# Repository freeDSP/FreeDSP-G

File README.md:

# FreeDSP-G (ADAU1467 DSP BOARD)

ADAU1467 DSP Board for Electic Guitar Players. The latest version design is 0.2  

## Features  

### Tube Electric Guitar Amplifier Simulator
* A simple single DSP board concept
* 6.5mm Phone Jack I/O connector
* KARAOKE (Play-along) feature
* Effect loop function with plug insert detection feature
* Stereo Output
* Headphones output
* Switchable Dual 7 Potentiometer Controls
* Dual Color LED indicator x1
* Single Color LED x1
* 3 Momentary-ON Footswitches with LED indicator
* Optical S/PDIF Input and Output
* 3.5mm Stereo Analog signal Input with plug insert detection and rotary volume control feature.
* USB-C Audio Input (44.1kHZ/48kHz)
* Embedded BM83 Bluetooth Audio Interface (Option)
* BGM mix level control (POT-7)
* DSP reset button
* Selfboot disable jumper
* Brite(Hi-Boost) Jumper
* Triodizer Head Amplifier with bypass option
* USBi 10P IDC pin-Header with Shoruld

Wiki Page: https://github.com/freeDSP/FreeDSP-G/wiki

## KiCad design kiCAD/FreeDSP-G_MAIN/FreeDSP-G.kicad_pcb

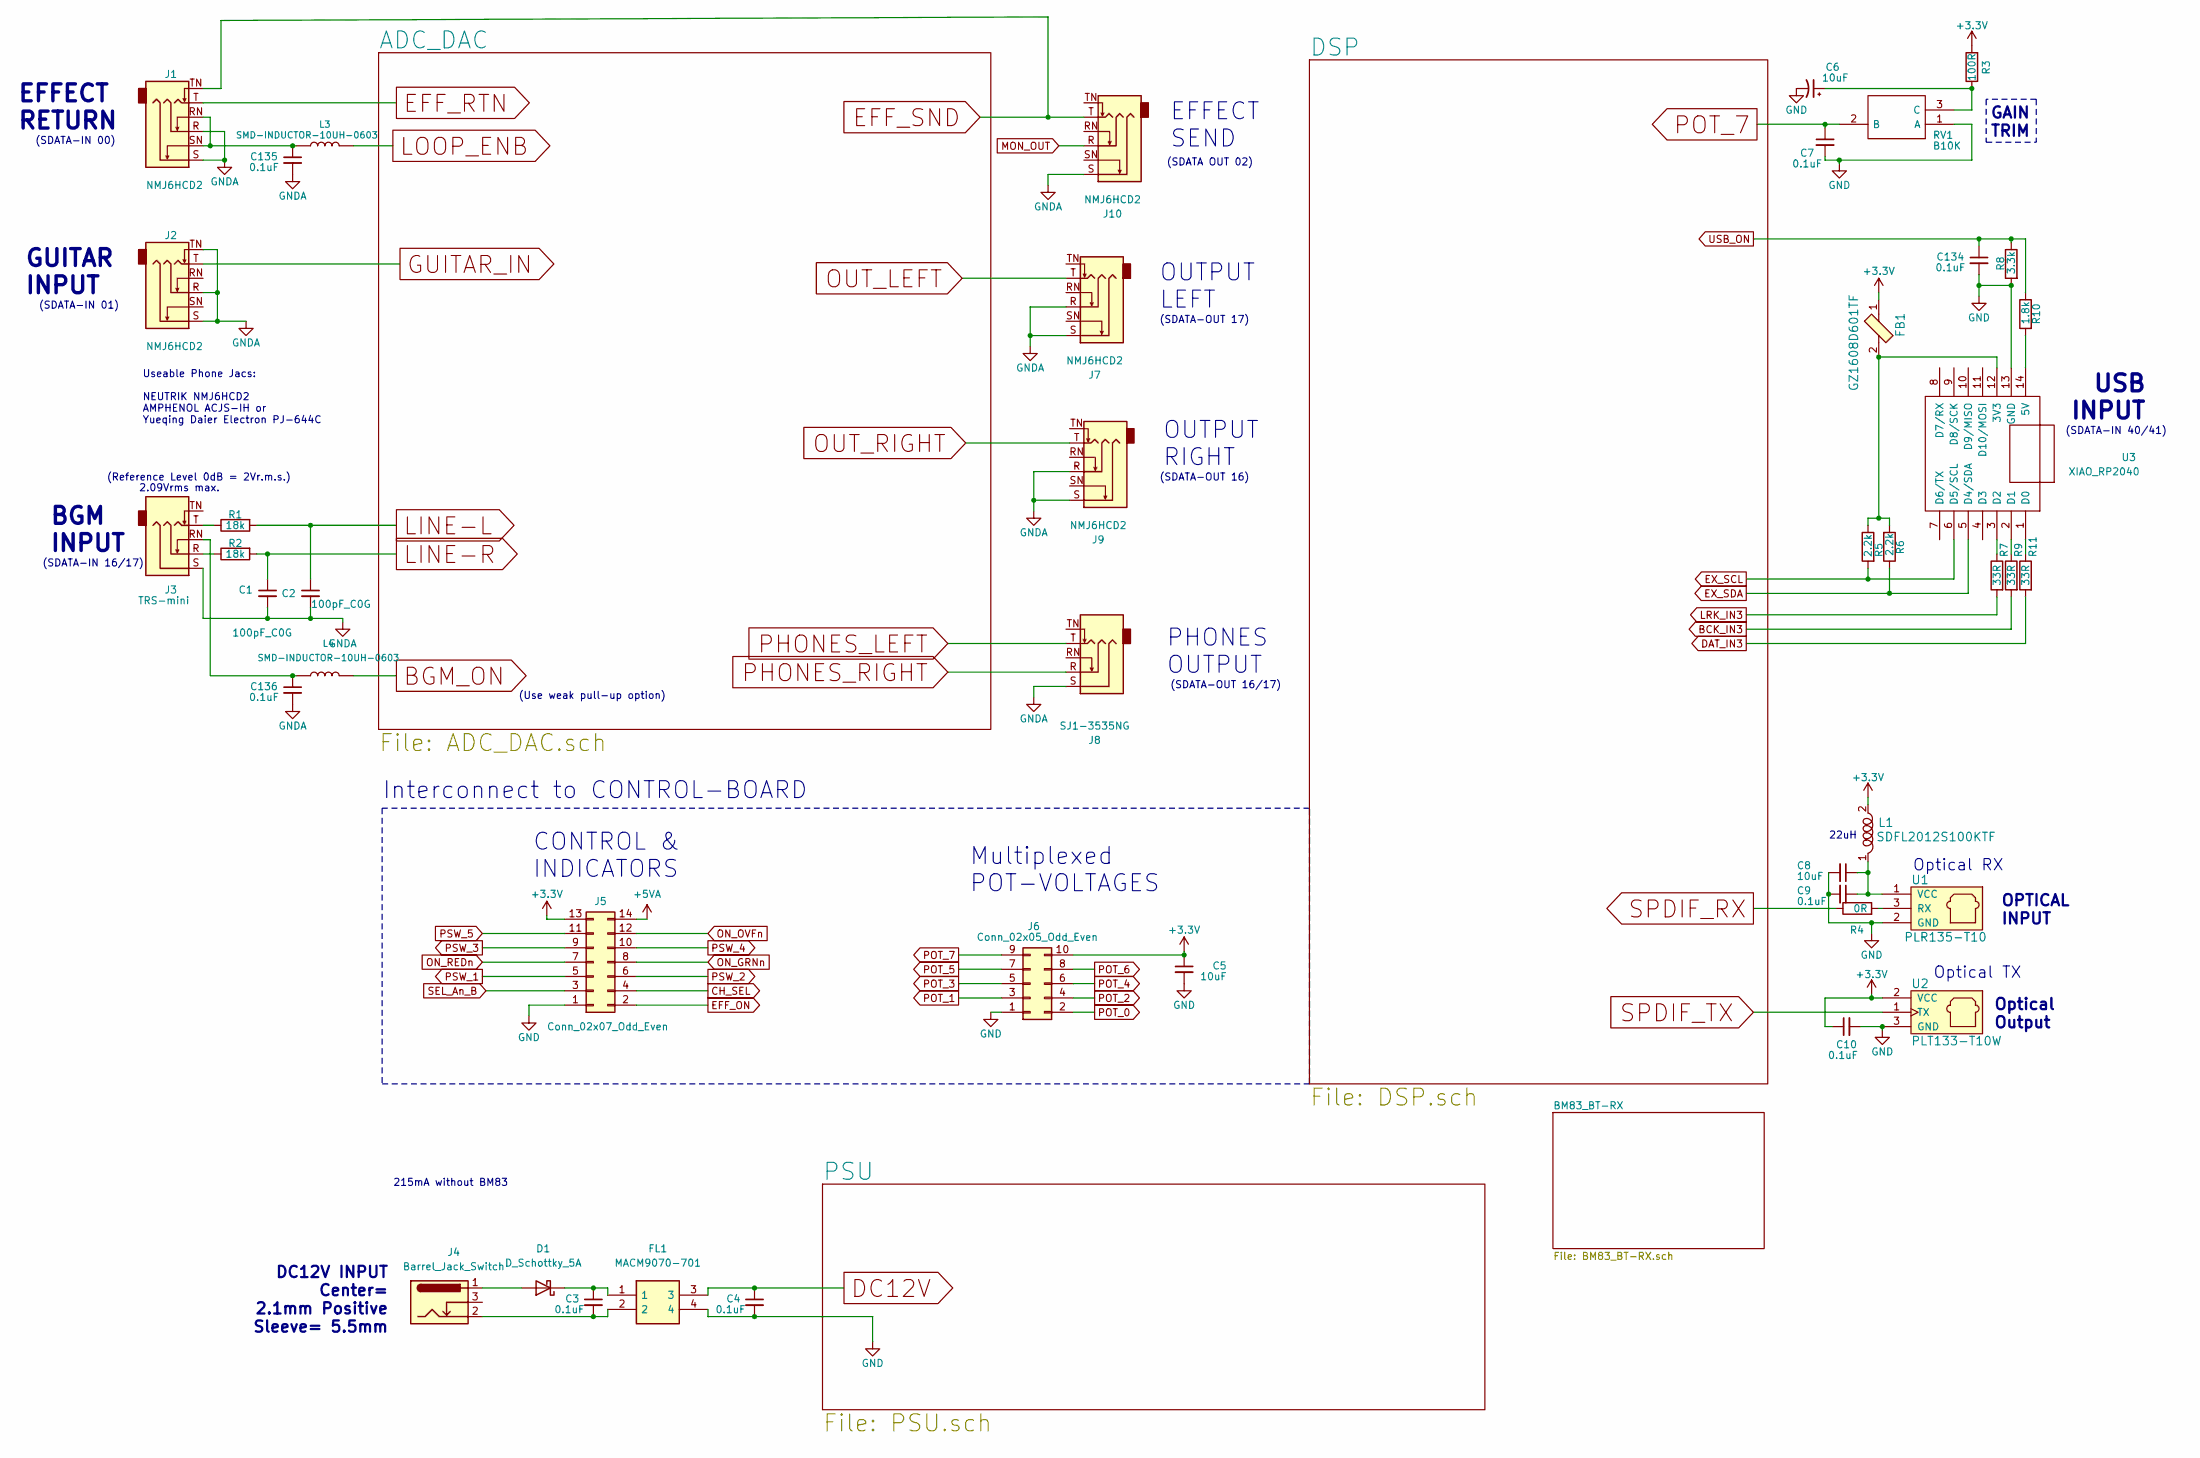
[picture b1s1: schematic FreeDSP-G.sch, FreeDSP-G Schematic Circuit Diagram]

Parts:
C1, C2: 100pF_C0G; C_0603_1608Metric_Pad1.08x0.95mm_HandSolder
C3, C4, C7, C9, C10, C134, C135, C136: 0.1uF; C_0603_1608Metric_Pad1.08x0.95mm_HandSolder
C5, C6, C8: 10uF; C_0805_2012Metric
D1: D_Schottky_5A; D_SMA
FB1: GZ1608D601TF; L_0603_1608Metric_Pad1.05x0.95mm_HandSolder; MPN BLM18AG601SN1D; Digi-Key_PN 490-1014-1-ND
FL1: MACM9070-701; ACM9070; Manufacturer_Part_Number ACM9070-701-2PL-TL01
J1, J2, J7, J9, J10: NMJ6HCD2; PJ-644C_NMJ6HCD2_ACJS-IH
J3: TRS-mini; Jack_3.5mm_CUI_SJ1-3535NG_Horizontal
J4: Barrel_Jack_Switch; BarrelJack_CUI_PJ-102AH_Horizontal
J5: Conn_02x07_Odd_Even; IDC-Header_2x07_P2.54mm_Horizontal
J6: Conn_02x05_Odd_Even; IDC-Header_2x05_P2.54mm_Horizontal
J8: SJ1-3535NG; Jack_3.5mm_CUI_SJ1-3535NG_Horizontal
L1: SDFL2012S100KTF; L_0805_2012Metric_Pad1.15x1.40mm_HandSolder; MPN 82473C; Digi-Key_PN 811-2477-1-ND
L3, L4: SMD-INDUCTOR-10UH-0603; L_0603_1608Metric; MPN SDFL1608S100KTF
R1, R2: 18k; R_0603_1608Metric_Pad0.98x0.95mm_HandSolder
R3: 100R; R_0603_1608Metric_Pad0.98x0.95mm_HandSolder
R4: 0R; R_0603_1608Metric_Pad0.98x0.95mm_HandSolder
R5, R6: 2.2k; R_0603_1608Metric_Pad0.98x0.95mm_HandSolder
R7, R9, R11: 33R; R_0603_1608Metric_Pad0.98x0.95mm_HandSolder
R8: 3.3k; R_0603_1608Metric_Pad0.98x0.95mm_HandSolder
R10: 1.8k; R_0603_1608Metric_Pad0.98x0.95mm_HandSolder
RV1: B10K; Potentiometer_Vishay_T73XX_Horizontal
U1: PLR135-T10
U2: PLT133-T10W
U3: XIAO_RP2040

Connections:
+3V3: C5.1, C10.1, FB1.1, J5.13, J6.10, L1.2, R3.2, U2.2 (VCC); also elsewhere on the board
+5VA: J5.14; also elsewhere on the board
BCK_IN3: R9.2; also elsewhere on the board
BGM_ON: L4.2; also elsewhere on the board
CH_SEL: J5.4; also elsewhere on the board
DAT_IN3: R11.2; also elsewhere on the board
DC12V: C4.1, FL1.3; also elsewhere on the board
EFF_ON: J5.2; also elsewhere on the board
EFF_RTN: J1.T; also elsewhere on the board
EFF_SND: J1.TN, J10.T; also elsewhere on the board
EX_SCL: R5.2, U3.6 (D5/SCL); also elsewhere on the board
EX_SDA: R6.1, U3.5 (D4/SDA); also elsewhere on the board
GND: C4.2, C5.2, C6.2, C7.2, C8.2, C9.2, C10.2, C134.2, FL1.4, J5.1, J6.1, R8.2, RV1.1 (A), U1.2 (GND), U2.3 (GND), U3.13 (GND); also elsewhere on the board
GNDA: C1.2, C2.2, C135.2, C136.2, J1.R, J1.S, J2.R, J2.S, J2.TN, J3.S, J7.R, J7.S, J8.S, J9.R, J9.S, J10.S; also elsewhere on the board
GUITAR_IN: J2.T; also elsewhere on the board
LINE-L: C2.1, R1.2; also elsewhere on the board
LINE-R: C1.1, R2.2; also elsewhere on the board
LOOP_ENB: L3.2; also elsewhere on the board
LRK_IN3: R7.2; also elsewhere on the board
MON_OUT: J10.R; also elsewhere on the board
unnamed: C3.1, D1.1 (K), FL1.1
unnamed: C3.2, FL1.2, J4.2
unnamed: C6.1, R3.1, RV1.3 (C)
unnamed: C8.1, C9.1, L1.1, U1.1 (VCC)
unnamed: C135.1, J1.RN, J1.SN, L3.1
unnamed: C136.1, J3.RN, L4.1
unnamed: D1.2 (A), J4.1
unnamed: FB1.2, R5.1, R6.2, U3.12 (3V3)
unnamed: J3.R, R2.1
unnamed: J3.T, R1.1
unnamed: R4.2, U1.3 (RX)
unnamed: R7.1, U3.3 (D2)
unnamed: R9.1, U3.2 (D1)
unnamed: R10.2, U3.14 (5V)
unnamed: R11.1, U3.1 (D0)
ON_GRNn: J5.8; also elsewhere on the board
ON_OVFn: J5.12; also elsewhere on the board
ON_REDn: J5.7; also elsewhere on the board
OUT_LEFT: J7.T; also elsewhere on the board
OUT_RIGHT: J9.T; also elsewhere on the board
PHONES_LEFT: J8.T; also elsewhere on the board
PHONES_RIGHT: J8.R; also elsewhere on the board
POT_0: J6.2; also elsewhere on the board
POT_1: J6.3; also elsewhere on the board
POT_2: J6.4; also elsewhere on the board
POT_3: J6.5; also elsewhere on the board
POT_4: J6.6; also elsewhere on the board
POT_5: J6.7; also elsewhere on the board
POT_6: J6.8; also elsewhere on the board
POT_7: C7.1, J6.9, RV1.2 (B); also elsewhere on the board
PSW_1: J5.5; also elsewhere on the board
PSW_2: J5.6; also elsewhere on the board
PSW_3: J5.9; also elsewhere on the board
PSW_4: J5.10; also elsewhere on the board
PSW_5: J5.11; also elsewhere on the board
SEL_An_B: J5.3; also elsewhere on the board
SPDIF_RX: R4.1; also elsewhere on the board
SPDIF_TX: U2.1 (TX); also elsewhere on the board
USB_ON: C134.1, R8.1, R10.1; also elsewhere on the board

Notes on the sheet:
DC12V INPUT Center= 2.1mm Positive Sleeve= 5.5mm
GUITAR INPUT
EFFECT RETURN
EFFECT SEND
PHONES OUTPUT
BGM INPUT
OUTPUT LEFT
OUTPUT RIGHT
(Reference Level 0dB = 2Vr.m.s.)
2.09Vrms max.
USB INPUT
CONTROL & INDICATORS
Multiplexed POT-VOLTAGES
Interconnect to CONTROL-BOARD
Optical Output
OPTICAL INPUT
22uH
Optical RX
Optical TX
GAIN TRIM
(Use weak pull-up option)
Useable Phone Jacs: NEUTRIK NMJ6HCD2 AMPHENOL ACJS-IH or Yueqing Daier Electron PJ-644C
215mA without BM83
(SDATA-IN 01)
(SDATA-IN 00)
(SDATA-IN 16/17)
(SDATA-IN 40/41)
(SDATA OUT 02)
(SDATA-OUT 17)
(SDATA-OUT 16)
(SDATA-OUT 16/17)

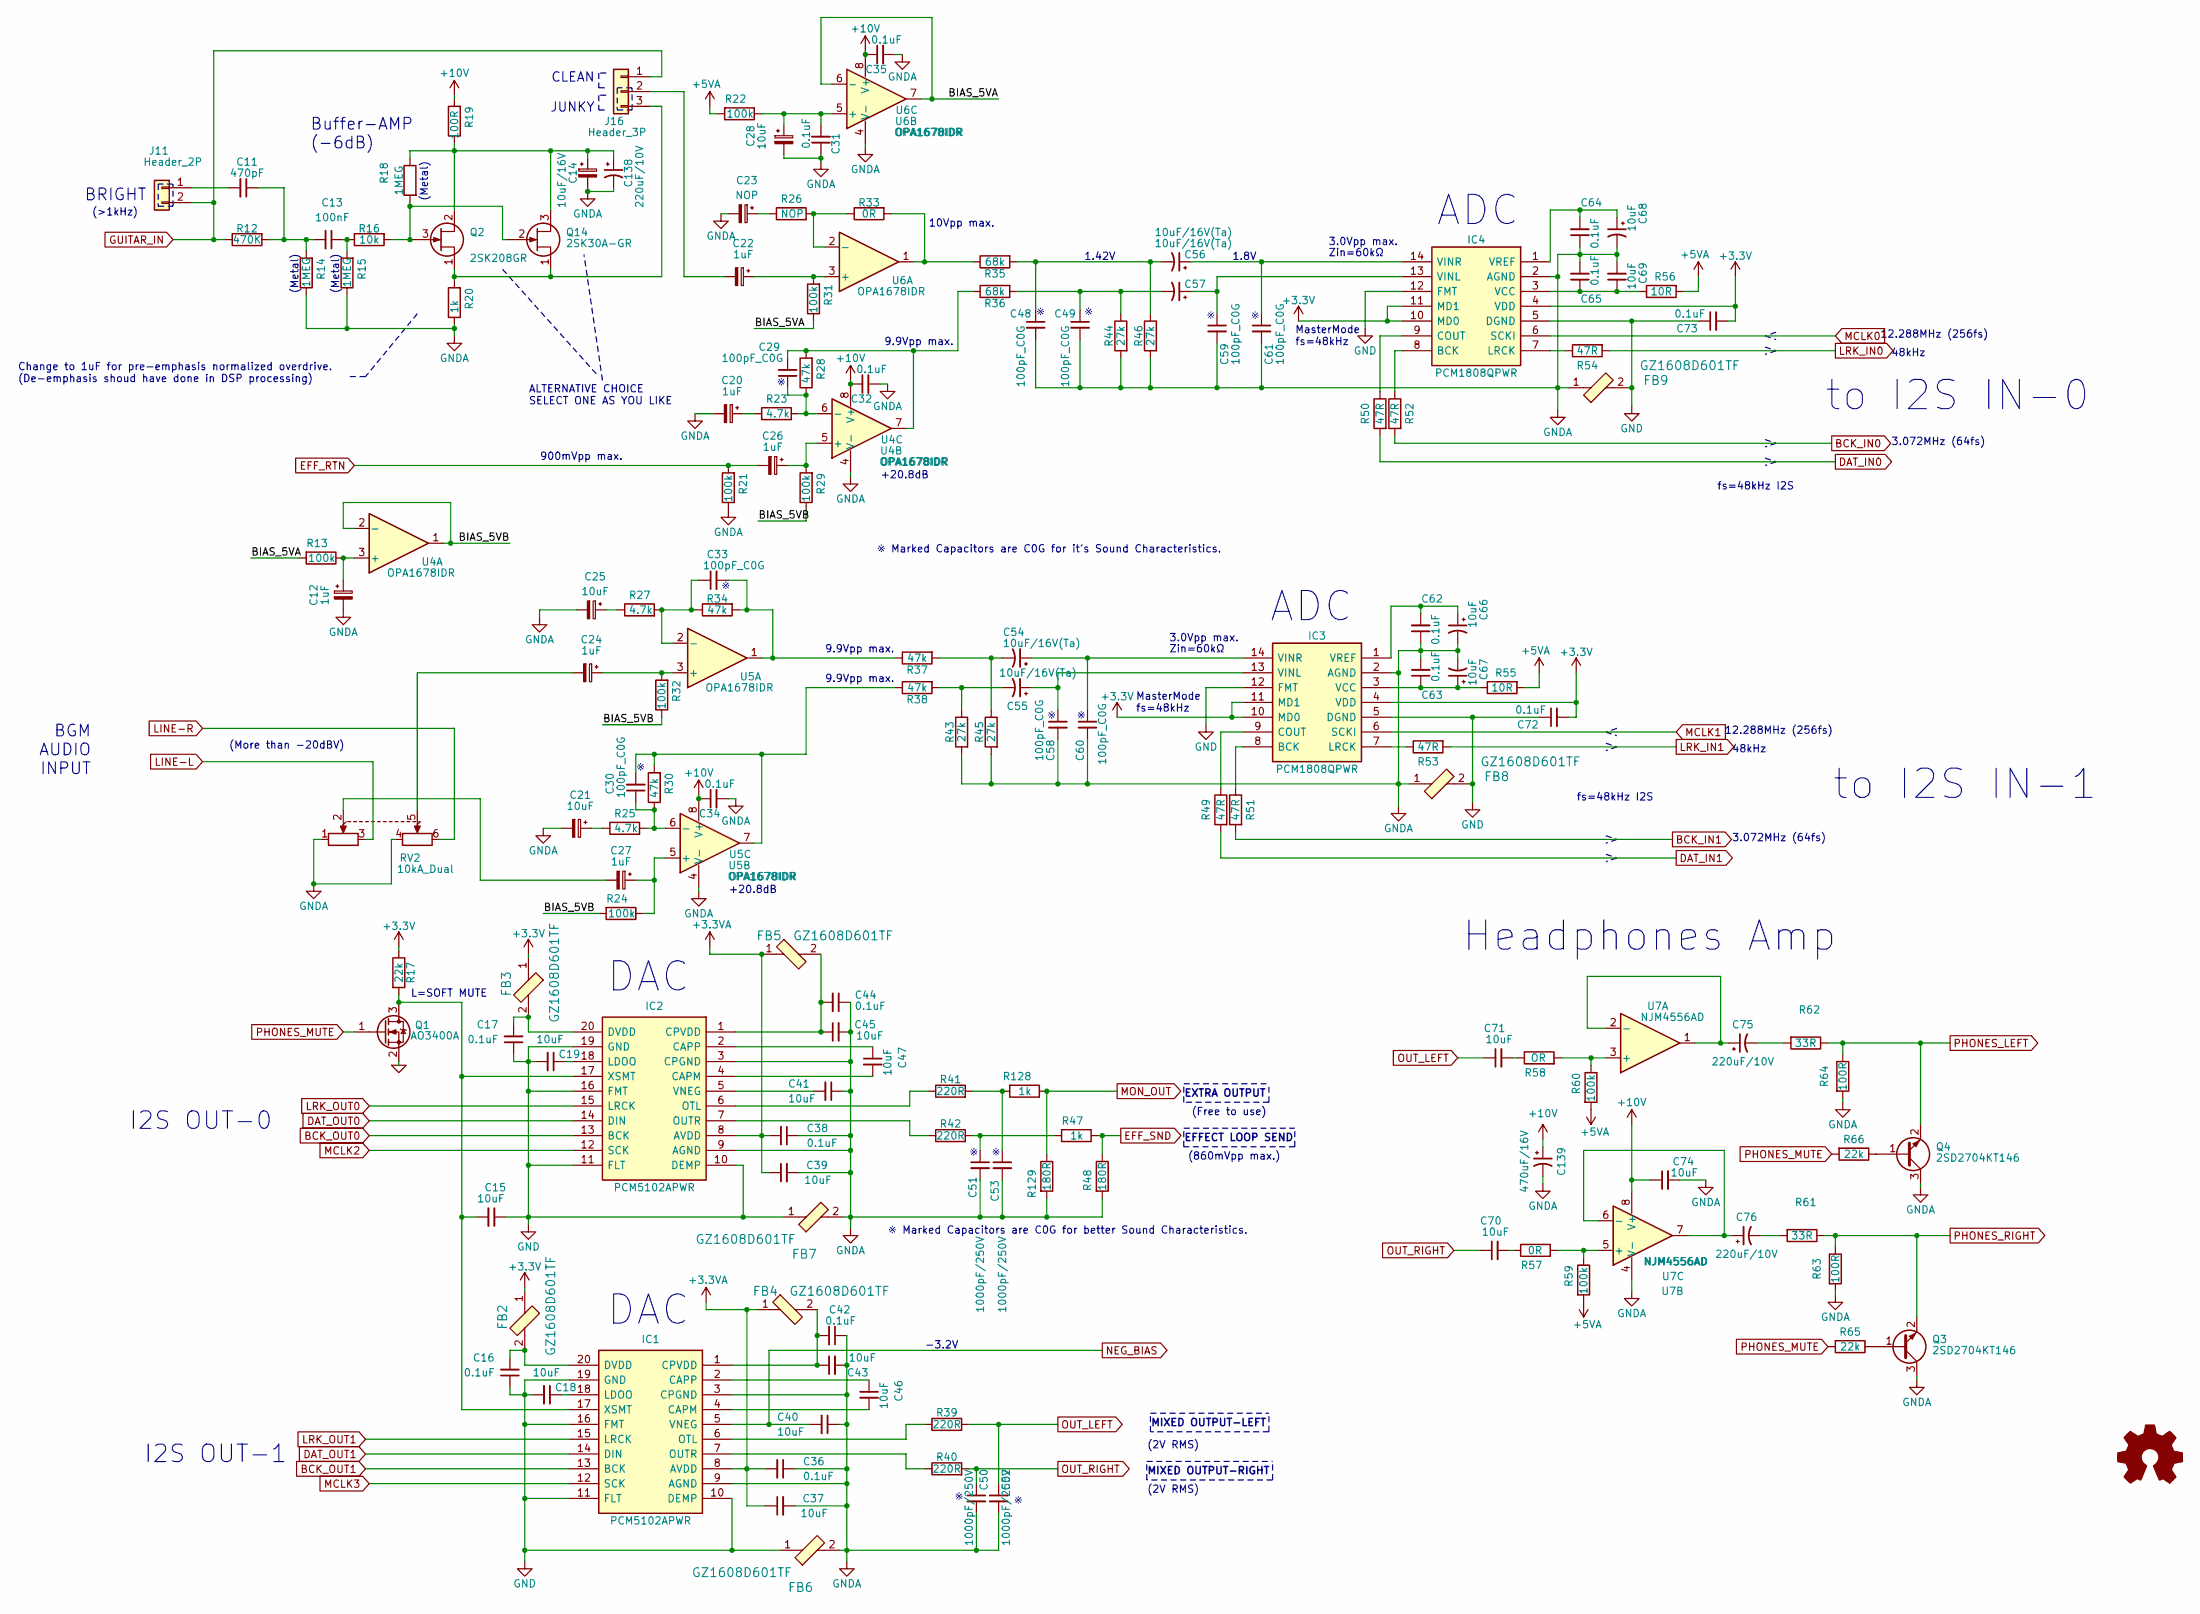
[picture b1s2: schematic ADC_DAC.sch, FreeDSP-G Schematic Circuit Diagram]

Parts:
C11: 470pF; C_0603_1608Metric_Pad1.08x0.95mm_HandSolder
C12, C20, C22, C24, C26, C27: 1uF; C_0805_2012Metric
C13: 100nF; C_0805_2012Metric
C14: 10uF/16V; CP_EIA-2012-12_Kemet-R
C15, C18, C19, C21, C25, C28, C37, C39, C40, C41, C43, C45, C46, C47, C66, C67, C68, C69, C70, C71, C74: 10uF; C_0805_2012Metric
C16, C17, C31, C32, C34, C35, C36, C38, C42, C44, C62, C63, C64, C65, C72, C73: 0.1uF; C_0603_1608Metric_Pad1.08x0.95mm_HandSolder
C23: NOP; C_0805_2012Metric
C29, C30, C33, C48, C49, C58, C59, C60, C61: 100pF_C0G; C_0603_1608Metric_Pad1.08x0.95mm_HandSolder
C50, C51, C52, C53: 1000pF/250V; C_0805_2012Metric
C54, C55, C56, C57: 10uF/16V(Ta); CP_Tantalum_Case-A_EIA-3216-18_Reflow
C75, C76, C138: 220uF/10V; CP_Radial_D7.5mm_P2.50mm
C139: 470uF/16V; CP_Radial_D10.0mm_P2.50mm_P5.00mm
FB2, FB3, FB4, FB5: GZ1608D601TF; L_0603_1608Metric_Pad1.05x0.95mm_HandSolder; MPN BLM18AG601SN1D; Digi-Key_PN 490-1014-1-ND
FB6, FB7, FB8, FB9: GZ1608D601TF; L_0603_1608Metric_Pad1.05x0.95mm_HandSolder; MPN BLM21PG331SN1D; Digi-Key_PN 490-5988-1-ND
IC1, IC2: PCM5102APWR; TSSOP-20_4.4x6.5mm_P0.65mm; Manufacturer_Part_Number PCM5102APWR
IC3, IC4: PCM1808QPWR; PCM1808QPWRQ1; Manufacturer_Part_Number PCM1808QPWRQ1
J11: Header_2P; PinHeader_1x02_P2.54mm_Vertical
J16: Header_3P; PinHeader_1x03_P2.54mm_Vertical
LOGO1: Logo_Open_Hardware_Small; LOGO_FREEDSP_600dpi
Q1: AO3400A; SOT-23
Q2: 2SK208GR; SC-59
Q3, Q4: 2SD2704KT146; SOT-23
Q14: 2SK30A-GR; TO-92_Inline_Narrow_Oval
R12: 470K; R_0603_1608Metric_Pad0.98x0.95mm_HandSolder
R13, R21, R22, R24, R29, R31, R32, R59, R60: 100k; R_0603_1608Metric_Pad0.98x0.95mm_HandSolder
R14, R15, R18: 1MEG; R_0603_1608Metric_Pad0.98x0.95mm_HandSolder
R16: 10k; R_0603_1608Metric_Pad0.98x0.95mm_HandSolder
R17, R65, R66: 22k; R_0603_1608Metric_Pad0.98x0.95mm_HandSolder
R19, R63, R64: 100R; R_0603_1608Metric_Pad0.98x0.95mm_HandSolder
R20, R47, R128: 1k; R_0603_1608Metric_Pad0.98x0.95mm_HandSolder
R23, R25, R27: 4.7k; R_0603_1608Metric_Pad0.98x0.95mm_HandSolder
R26: NOP; R_0603_1608Metric_Pad0.98x0.95mm_HandSolder
R28, R30, R34, R37, R38: 47k; R_0603_1608Metric_Pad0.98x0.95mm_HandSolder
R33, R57: 0R; R_0603_1608Metric_Pad0.98x0.95mm_HandSolder
R35, R36: 68k; R_0603_1608Metric_Pad0.98x0.95mm_HandSolder
R39, R40, R41, R42: 220R; R_0603_1608Metric_Pad0.98x0.95mm_HandSolder
R43, R44, R45, R46: 27k; R_0603_1608Metric_Pad0.98x0.95mm_HandSolder
R48, R129: 180R; R_0603_1608Metric_Pad0.98x0.95mm_HandSolder
R49, R50, R51, R52, R53, R54: 47R; R_0603_1608Metric_Pad0.98x0.95mm_HandSolder
R55, R56: 10R; R_0603_1608Metric_Pad0.98x0.95mm_HandSolder
R58: OR; R_0603_1608Metric_Pad0.98x0.95mm_HandSolder
R61, R62: 33R; R_0603_1608Metric_Pad0.98x0.95mm_HandSolder
RV2: 10kA_Dual; RK09712
U4, U5, U6: OPA1678IDR; SOIC-8_3.9x4.9mm_P1.27mm
U7: NJM4556AD; DIP-8_W7.62mm

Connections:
+3.3VA: C36.2, C37.1, C38.2, C39.1, FB4.1, FB5.1, IC1.8 (AVDD), IC2.8 (AVDD); also elsewhere on the board
+3V3: C72.2, C73.2, FB2.1, FB3.1, IC3.4 (VDD), IC3.10 (MD0), IC3.11 (MD1), IC4.4 (VDD), IC4.10 (MD0), IC4.11 (MD1), R17.1; also elsewhere on the board
+5VA: R22.2, R55.2, R56.2, R59.2, R60.2; also elsewhere on the board
+10V: C32.1, C34.1, C35.1, C74.1, C139.1, R19.2, U4.8 (V+), U5.8 (V+), U6.8 (V+), U7.8 (V+); also elsewhere on the board
/ADC_DAC/BIAS_5VA: R13.2, R31.1, U6.6 (-), U6.7
/ADC_DAC/BIAS_5VB: R24.2, R29.1, R32.1, U4.1, U4.2 (-)
BCK_IN0: R52.2; also elsewhere on the board
BCK_IN1: R51.2; also elsewhere on the board
BCK_OUT0: IC2.13 (BCK); also elsewhere on the board
BCK_OUT1: IC1.13 (BCK); also elsewhere on the board
DAT_IN0: R50.2; also elsewhere on the board
DAT_IN1: R49.2; also elsewhere on the board
DAT_OUT0: IC2.14 (DIN); also elsewhere on the board
DAT_OUT1: IC1.14 (DIN); also elsewhere on the board
EFF_RTN: C26.2, R21.2; also elsewhere on the board
EFF_SND: R47.1, R48.1; also elsewhere on the board
GND: C15.1, C16.1, C17.1, C18.2, C19.2, C72.1, C73.1, FB6.1, FB7.1, FB8.2, FB9.2, IC1.10 (DEMP), IC1.11 (FLT), IC1.16 (FMT), IC1.19 (GND), IC2.10 (DEMP), IC2.11 (FLT), IC2.16 (FMT), IC2.19 (GND), IC3.5 (DGND), IC3.12 (FMT), IC4.5 (DGND), IC4.12 (FMT), Q1.2 (S); also elsewhere on the board
GNDA: C12.2, C14.2, C20.2, C21.2, C23.2, C25.2, C28.2, C31.1, C32.2, C34.2, C35.2, C36.1, C37.2, C38.1, C39.2, C40.1, C41.1, C42.1, C43.2, C44.1, C45.2, C48.2, C49.2, C50.2, C51.2, C52.2, C53.2, C58.2, C59.2, C60.2, C61.2, C62.1, C63.2, C64.1, C65.2, C66.2, C67.2, C68.2, C69.2, C74.2, C138.2, C139.2, FB6.2, FB7.2, FB8.1, FB9.1, IC1.3 (CPGND), IC1.9 (AGND), IC2.3 (CPGND), IC2.9 (AGND), IC3.2 (AGND), IC4.2 (AGND), Q3.3 (C), Q4.3 (C), R14.1, R15.1, R20.1, R21.1, R43.2, R44.2, R45.2, R46.2, R48.2, R63.2, R64.2, R129.2, RV2.1, RV2.4, U4.4 (V-), U5.4 (V-), U6.4 (V-), U7.4 (V-); also elsewhere on the board
GUITAR_IN: J11.2, J16.1, R12.1; also elsewhere on the board
LINE-L: RV2.3; also elsewhere on the board
LINE-R: RV2.6; also elsewhere on the board
LRK_IN0: R54.2; also elsewhere on the board
LRK_IN1: R53.2; also elsewhere on the board
LRK_OUT0: IC2.15 (LRCK); also elsewhere on the board
LRK_OUT1: IC1.15 (LRCK); also elsewhere on the board
MCLK0: IC4.6 (SCKI); also elsewhere on the board
MCLK1: IC3.6 (SCKI); also elsewhere on the board
MCLK2: IC2.12 (SCK); also elsewhere on the board
MCLK3: IC1.12 (SCK); also elsewhere on the board
MON_OUT: R128.1, R129.1; also elsewhere on the board
NEG_BIAS: C40.2, IC1.5 (VNEG); also elsewhere on the board
unnamed: C11.1, C13.2, R12.2, R14.2
unnamed: C11.2, J11.1
unnamed: C12.1, R13.1, U4.3 (+)
unnamed: C13.1, R15.2, R16.1
unnamed: C15.2, IC1.17 (XSMT), IC2.17 (XSMT), Q1.3 (D), R17.2
unnamed: C16.2, FB2.2, IC1.20 (DVDD)
unnamed: C17.2, FB3.2, IC2.20 (DVDD)
unnamed: C18.1, IC1.18 (LDOO)
unnamed: C19.1, IC2.18 (LDOO)
unnamed: C20.1, R23.1
unnamed: C21.1, R25.1
unnamed: C22.1, R31.2, U6.3 (+)
unnamed: C22.2, J16.2
unnamed: C23.1, R26.1
unnamed: C24.1, R32.2, U5.3 (+)
unnamed: C24.2, RV2.5
unnamed: C25.1, R27.1
unnamed: C26.1, R29.2, U4.5 (+)
unnamed: C27.1, R24.1, U5.5 (+)
unnamed: C27.2, RV2.2
unnamed: C28.1, C31.2, R22.1, U6.5 (+)
unnamed: C29.1, R23.2, R28.1, U4.6 (-)
unnamed: C29.2, R28.2, R36.1, U4.7
unnamed: C30.1, R25.2, R30.1, U5.6 (-)
unnamed: C30.2, R30.2, R38.1, U5.7
unnamed: C33.1, R27.2, R34.1, U5.2 (-)
unnamed: C33.2, R34.2, R37.1, U5.1
unnamed: C41.2, IC2.5 (VNEG)
unnamed: C42.2, C43.1, FB4.2, IC1.1 (CPVDD)
unnamed: C44.2, C45.1, FB5.2, IC2.1 (CPVDD)
unnamed: C46.1, IC1.2 (CAPP)
unnamed: C46.2, IC1.4 (CAPM)
unnamed: C47.1, IC2.2 (CAPP)
unnamed: C47.2, IC2.4 (CAPM)
unnamed: C48.1, C56.2, R35.2, R46.1
unnamed: C49.1, C57.2, R36.2, R44.1
unnamed: C51.1, R42.2, R47.2
unnamed: C53.1, R41.2, R128.2
unnamed: C54.1, C60.1, IC3.14 (VINR)
unnamed: C54.2, R37.2, R45.1
unnamed: C55.1, C58.1, IC3.13 (VINL)
unnamed: C55.2, R38.2, R43.1
unnamed: C56.1, C61.1, IC4.14 (VINR)
unnamed: C57.1, C59.1, IC4.13 (VINL)
unnamed: C62.2, C66.1, IC3.1 (VREF)
unnamed: C63.1, C67.1, IC3.3 (VCC), R55.1
unnamed: C64.2, C68.1, IC4.1 (VREF)
unnamed: C65.1, C69.1, IC4.3 (VCC), R56.1
unnamed: C70.2, R57.1
unnamed: C71.2, R58.1
unnamed: C75.1, U7.1, U7.2 (-)
unnamed: C75.2, R62.2
unnamed: C76.1, U7.6 (-), U7.7
unnamed: C76.2, R61.2
unnamed: C14.1, C138.1, Q2.2 (D), Q14.3 (D), R18.1, R19.1
unnamed: IC1.6 (OTL), R39.1
unnamed: IC1.7 (OUTR), R40.1
unnamed: IC2.6 (OTL), R41.1
unnamed: IC2.7 (OUTR), R42.1
unnamed: IC3.7 (LRCK), R53.1
unnamed: IC3.8 (BCK), R51.1
unnamed: IC3.9 (COUT), R49.1
unnamed: IC4.7 (LRCK), R54.1
unnamed: IC4.8 (BCK), R52.1
unnamed: IC4.9 (COUT), R50.1
unnamed: J16.3, Q2.1 (S), Q14.1 (S), R20.2
unnamed: Q3.1 (B), R65.1
unnamed: Q4.1 (B), R66.1
unnamed: Q2.3 (G), Q14.2 (G), R16.2, R18.2
unnamed: R26.2, R33.1, U6.2 (-)
unnamed: R33.2, R35.1, U6.1
unnamed: R57.2, R59.1, U7.5 (+)
unnamed: R58.2, R60.1, U7.3 (+)
OUT_LEFT: C52.1, C71.1, R39.2; also elsewhere on the board
OUT_RIGHT: C50.1, C70.1, R40.2; also elsewhere on the board
PHONES_LEFT: Q4.2 (E), R62.1, R64.1; also elsewhere on the board
PHONES_MUTE: Q1.1 (G), R65.2, R66.2; also elsewhere on the board
PHONES_RIGHT: Q3.2 (E), R61.1, R63.1; also elsewhere on the board

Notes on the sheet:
Buffer-AMP (-6dB)
3.0Vpp max.
Zin=60kΩ
10Vpp max.
fs=48kHz I2S
12.288MHz (256fs)
48kHz
BGM AUDIO INPUT
MasterMode fs=48kHz
9.9Vpp max.
+20.8dB
900mVpp max.
(Metal)
3.072MHz (64fs)
BRIGHT
I2S OUT-0
to I2S IN-0
L=SOFT MUTE
EXTRA OUTPUT
EFFECT LOOP SEND
(860mVpp max.)
(Free to use)
※ Marked Capacitors are C0G for better Sound Characteristics.
DAC
to I2S IN-1
I2S OUT-1
MIXED OUTPUT-LEFT
MIXED OUTPUT-RIGHT
(2V RMS)
(>1kHz)
(More than -20dBV)
ADC
Headphones Amp
※ Marked Capacitors are C0G for it’s Sound Characteristics.
-3.2V
Change to 1uF for pre-emphasis normalized overdrive. (De-emphasis shoud have done in DSP processing)
ALTERNATIVE CHOICE SELECT ONE AS YOU LIKE
CLEAN JUNKY
1.8V
1.42V

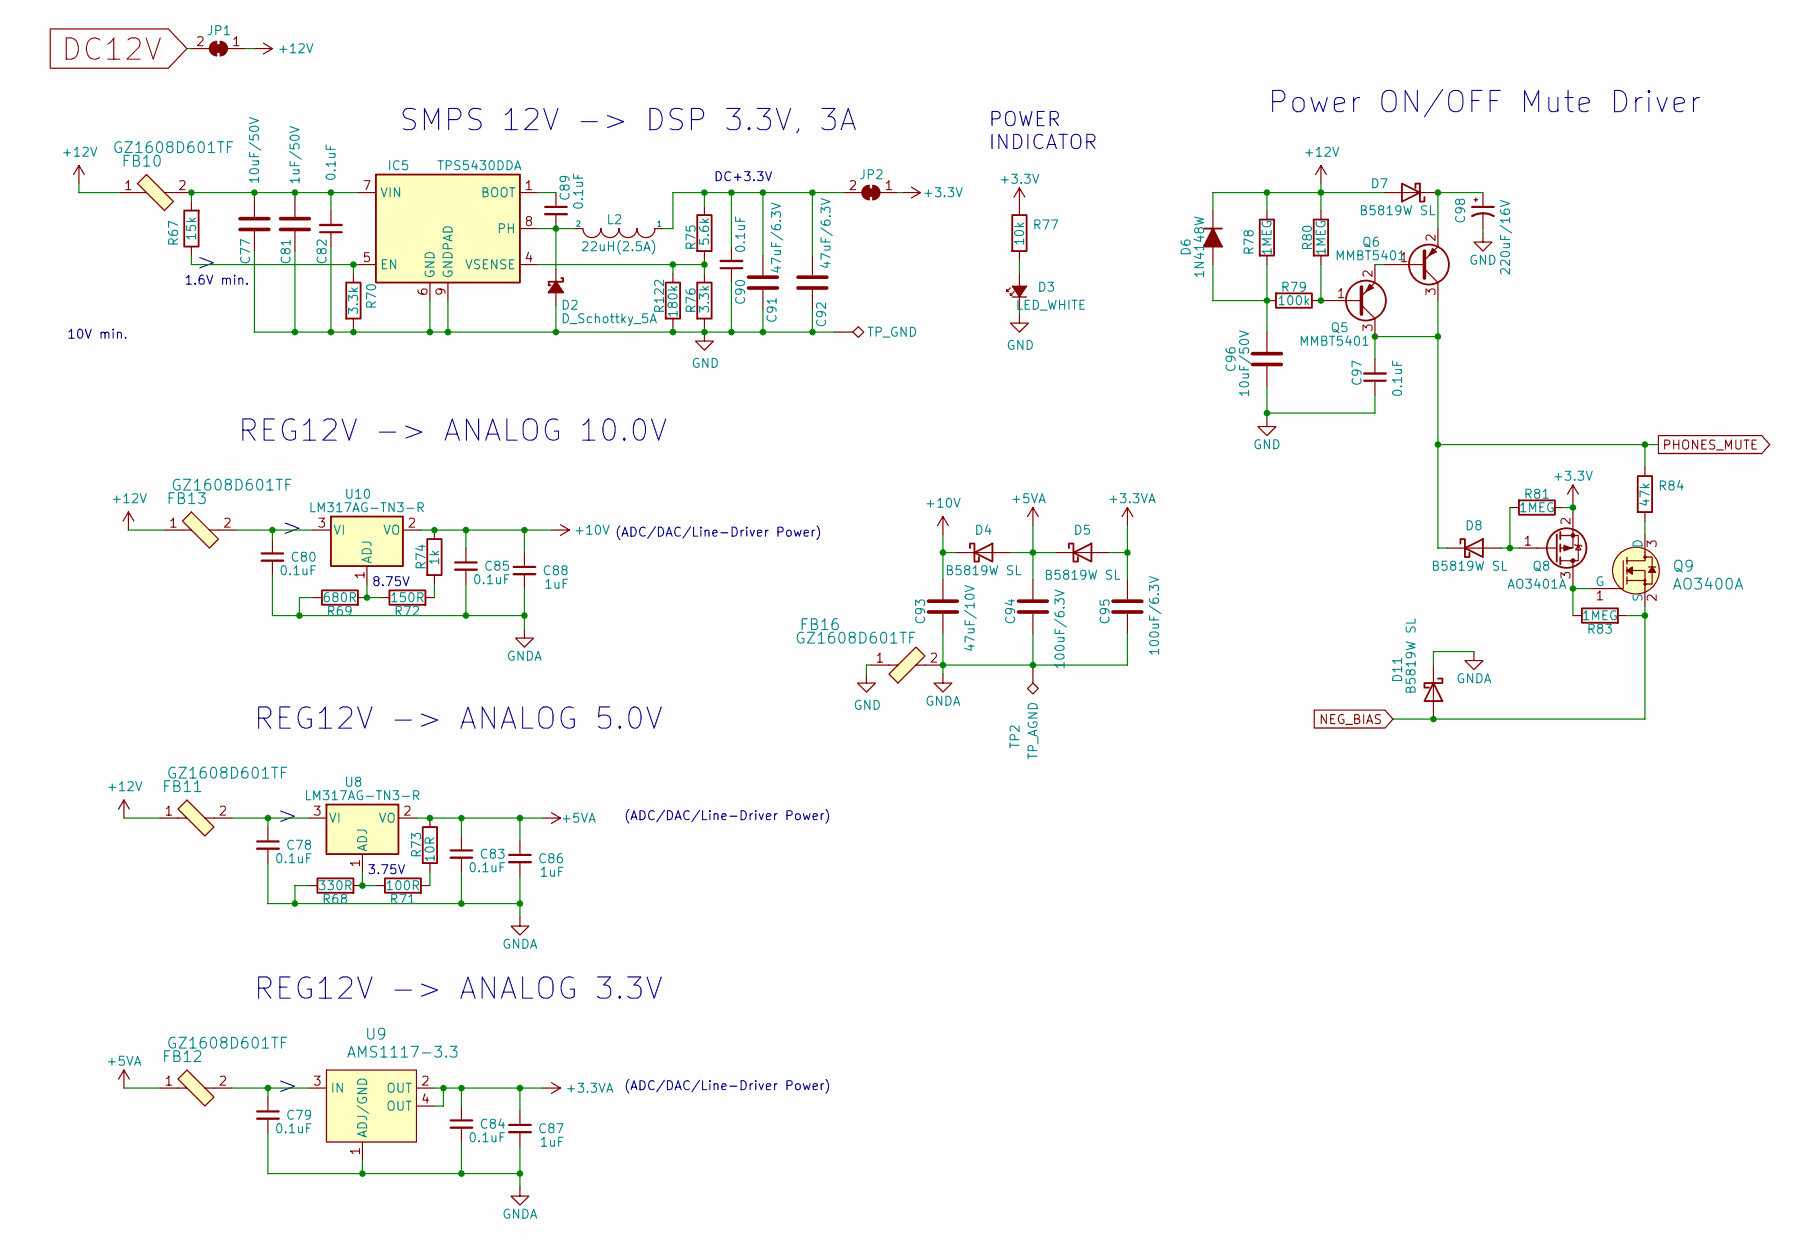
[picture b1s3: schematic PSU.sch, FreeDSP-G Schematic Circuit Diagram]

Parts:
C77, C96: 10uF/50V; C_0805_2012Metric
C78, C79, C80, C82, C83, C84, C85, C89, C90, C97: 0.1uF; C_0603_1608Metric_Pad1.08x0.95mm_HandSolder
C81: 1uF/50V; C_0805_2012Metric
C86, C87, C88: 1uF; C_0805_2012Metric
C91, C92: 47uF/6.3V; C_0805_2012Metric
C93: 47uF/10V; C_1206_3216Metric
C94, C95: 100uF/6.3V; C_1206_3216Metric
C98: 220uF/16V; CP_Radial_D7.5mm_P2.50mm
D2: D_Schottky_5A; D_SMA
D3: LED_WHITE; LED_0603_1608Metric_Castellated
D4, D5, D7, D8, D11: B5819W SL; D_SOD-123
D6: 1N4148W; D_SOD-123
FB10, FB11, FB12, FB13: GZ1608D601TF; L_0603_1608Metric_Pad1.05x0.95mm_HandSolder; MPN BLM18AG601SN1D; Digi-Key_PN 490-1014-1-ND
FB16: GZ1608D601TF; L_0603_1608Metric_Pad1.05x0.95mm_HandSolder; MPN BLM21PG331SN1D; Digi-Key_PN 490-5988-1-ND
IC5: TPS5430DDA; TI_SO-PowerPAD-8_ThermalVias
JP1, JP2: SolderJumper_3_Bridged12; SolderJumper-2_P1.3mm_Bridged_RoundedPad1.0x1.5mm
L2: 22uH(2.5A); L_Taiyo-Yuden_NR-60xx_HandSoldering
Q5, Q6: MMBT5401; SOT-23
Q8: AO3401A; SOT-23; Manufacturer_Part_Number DMG3415U-7; Mouser Part Number 621-DMG3415U-7
Q9: AO3400A; SOT-23; MPN 2N7002; Digi-Key_PN 2N7002NCT-ND
R67: 15k; R_0603_1608Metric_Pad0.98x0.95mm_HandSolder
R68: 330R; R_0603_1608Metric_Pad0.98x0.95mm_HandSolder
R69: 680R; R_0603_1608Metric_Pad0.98x0.95mm_HandSolder
R70, R76: 3.3k; R_0603_1608Metric_Pad0.98x0.95mm_HandSolder
R71: 100R; R_0603_1608Metric_Pad0.98x0.95mm_HandSolder
R72: 150R; R_0603_1608Metric_Pad0.98x0.95mm_HandSolder
R73: 10R; R_0603_1608Metric_Pad0.98x0.95mm_HandSolder
R74: 1k; R_0603_1608Metric_Pad0.98x0.95mm_HandSolder
R75: 5.6k; R_0603_1608Metric_Pad0.98x0.95mm_HandSolder
R77: 10k; R_0603_1608Metric_Pad0.98x0.95mm_HandSolder
R78, R80, R81, R83: 1MEG; R_0603_1608Metric_Pad0.98x0.95mm_HandSolder
R79: 100k; R_0603_1608Metric_Pad0.98x0.95mm_HandSolder
R84: 47k; R_0603_1608Metric_Pad0.98x0.95mm_HandSolder
R122: 180k; R_0603_1608Metric_Pad0.98x0.95mm_HandSolder
TP1: TP_GND; TestPoint_THTPad_1.5x1.5mm_Drill0.7mm
TP2: TP_AGND; TestPoint_THTPad_1.5x1.5mm_Drill0.7mm
U8, U10: LM317AG-TN3-R; TO-252-2
U9: AMS1117-3.3; SOT-223

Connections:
+3.3VA: C84.1, C87.1, C95.1, D5.2 (A), U9.2 (OUT), U9.4 (OUT); also elsewhere on the board
+3V3: JP2.1 (A), Q8.2 (S), R77.1, R81.1; also elsewhere on the board
+5VA: C83.1, C86.1, C94.1, D4.2 (A), D5.1 (K), FB12.1, R73.1, U8.2 (VO); also elsewhere on the board
+10V: C85.1, C88.1, C93.1, D4.1 (K), R74.1, U10.2 (VO); also elsewhere on the board
+12V: D6.1 (K), D7.2 (A), FB10.1, FB11.1, FB13.1, JP1.1 (A), R78.1, R80.1
DC12V: JP1.2 (B); also elsewhere on the board
GND: C77.2, C81.2, C82.1, C90.1, C91.2, C92.2, C96.2, C97.1, C98.2, D2.2 (A), D3.1 (K), FB16.1, IC5.6 (GND), IC5.9 (GNDPAD), R70.2, R76.2, R122.2, TP1.1; also elsewhere on the board
GNDA: C78.2, C79.2, C80.2, C83.2, C84.2, C85.2, C86.2, C87.2, C88.2, C93.2, C94.2, C95.2, D11.1 (K), FB16.2, R68.1, R69.1, TP2.1, U9.1 (ADJ/GND); also elsewhere on the board
NEG_BIAS: D11.2 (A), Q9.2 (S), R83.2; also elsewhere on the board
unnamed: C77.1, C81.1, C82.2, FB10.2, IC5.7 (VIN), R67.2
unnamed: C78.1, FB11.2, U8.3 (VI)
unnamed: C79.1, FB12.2, U9.3 (IN)
unnamed: C80.1, FB13.2, U10.3 (VI)
unnamed: C89.1, IC5.1 (BOOT)
unnamed: C89.2, D2.1 (K), IC5.8 (PH), L2.2
unnamed: C90.2, C91.1, C92.1, JP2.2 (B), L2.1, R75.1
unnamed: C96.1, D6.2 (A), R78.2, R79.2
unnamed: C98.1, D7.1 (K), Q6.2 (E)
unnamed: D3.2 (A), R77.2
unnamed: D8.2 (A), Q8.1 (G), R81.2
unnamed: IC5.4 (VSENSE), R75.2, R76.1, R122.1
unnamed: IC5.5 (EN), R67.1, R70.1
unnamed: Q5.1 (B), R79.1, R80.2
unnamed: Q5.2 (E), Q6.1 (B)
unnamed: Q8.3 (D), Q9.1 (G), R83.1
unnamed: Q9.3 (D), R84.2
unnamed: R68.2, R71.1, U8.1 (ADJ)
unnamed: R69.2, R72.1, U10.1 (ADJ)
unnamed: R71.2, R73.2
unnamed: R72.2, R74.2
PHONES_MUTE: C97.2, D8.1 (K), Q5.3 (C), Q6.3 (C), R84.1; also elsewhere on the board

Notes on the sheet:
DC+3.3V
SMPS 12V -> DSP 3.3V, 3A
POWER INDICATOR
Power ON/OFF Mute Driver
(ADC/DAC/Line-Driver Power)
1.6V min.
8.75V
REG12V -> ANALOG 10.0V
10V min.
3.75V
REG12V -> ANALOG 5.0V
REG12V -> ANALOG 3.3V

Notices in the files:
parts and their libraries:
Copyright 2016 Accelerated Designs. All rights reserved.
